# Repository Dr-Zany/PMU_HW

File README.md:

# PMU_HW
Hardware for the PMU

LP2950CZ-5.0/NOPB

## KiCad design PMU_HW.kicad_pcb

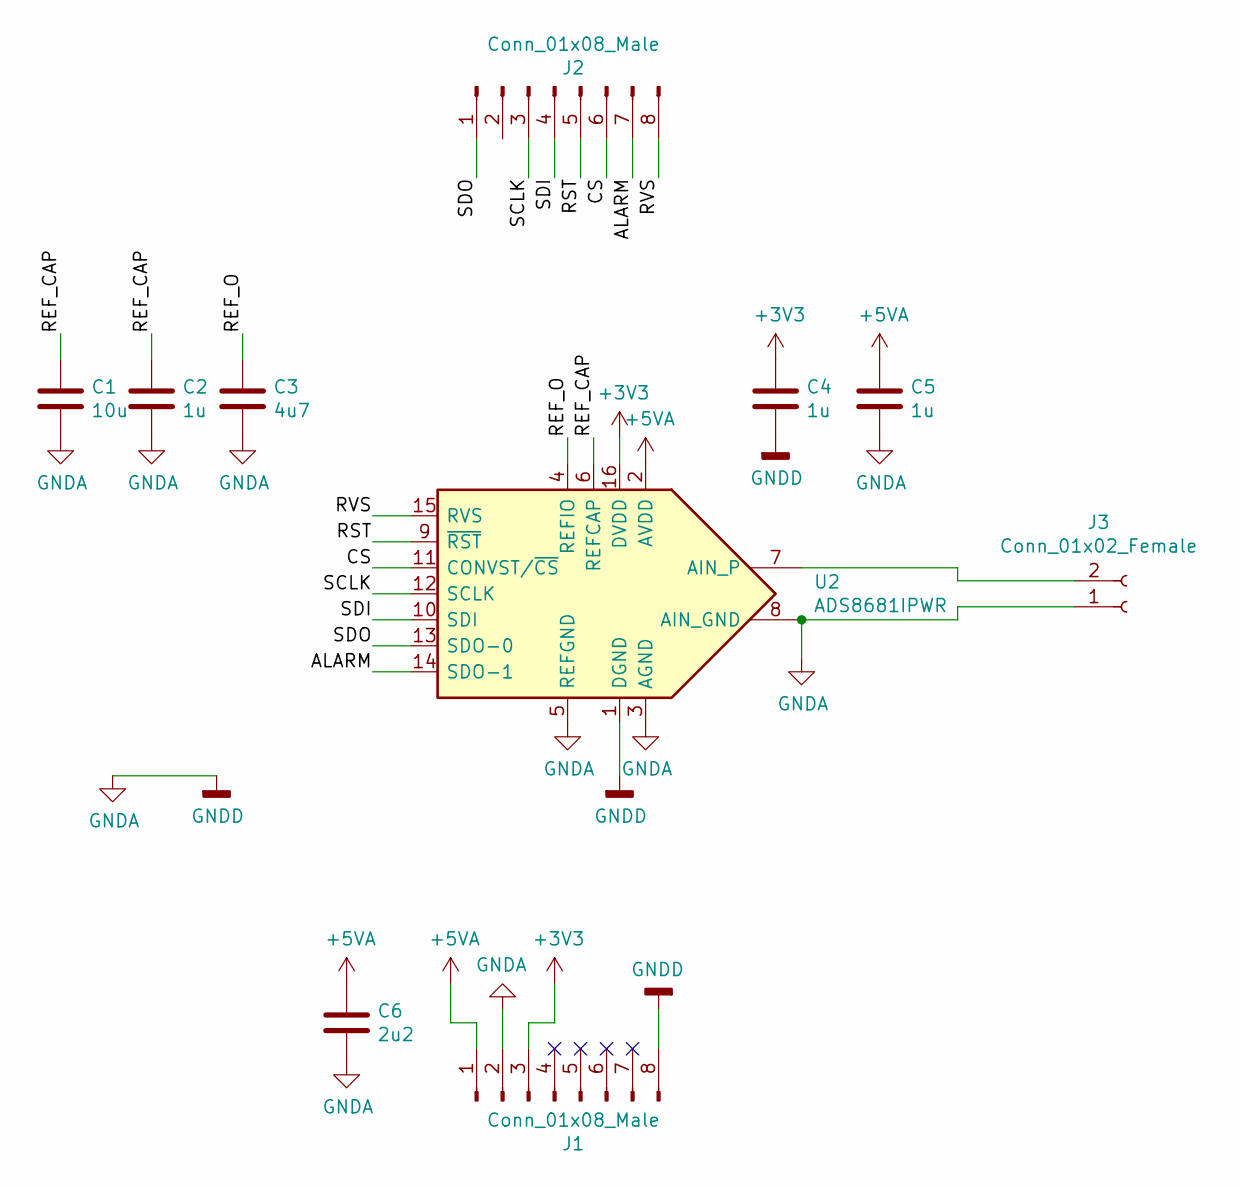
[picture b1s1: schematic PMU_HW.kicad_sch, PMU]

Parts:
C1: 10u; C_0805_2012Metric_Pad1.18x1.45mm_HandSolder
C2, C4, C5: 1u; C_0603_1608Metric_Pad1.08x0.95mm_HandSolder
C3: 4u7; C_0805_2012Metric_Pad1.18x1.45mm_HandSolder
C6: 2u2; C_0603_1608Metric_Pad1.08x0.95mm_HandSolder
J1, J2: Conn_01x08_Male; PinHeader_1x08_P2.54mm_Vertical
J3: Conn_01x02_Female; PinHeader_1x02_P2.54mm_Horizontal
U2: ADS8681IPWR; TSSOP-16_4.4x5mm_P0.65mm

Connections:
+3V3: C4.1, J1.3, U2.16 (DVDD)
+5VA: C5.1, C6.1, J1.1, U2.2 (AVDD)
/ALARM: J2.7, U2.14 (SDO-1)
/CS: J2.6, U2.11 (CONVST/~CS)
/REF_CAP: C1.1, C2.1, U2.6 (REFCAP)
/REF_O: C3.1, U2.4 (REFIO)
/RST: J2.5, U2.9 (~RST)
/RVS: J2.8, U2.15 (RVS)
/SCLK: J2.3, U2.12 (SCLK)
/SDI: J2.4, U2.10 (SDI)
/SDO: J2.1, U2.13 (SDO-0)
GNDA: C1.2, C2.2, C3.2, C4.2, C5.2, C6.2, J1.2, J1.8, J3.1, U2.1 (DGND), U2.3 (AGND), U2.5 (REFGND), U2.8 (AIN_GND)
unnamed: J3.2, U2.7 (AIN_P)

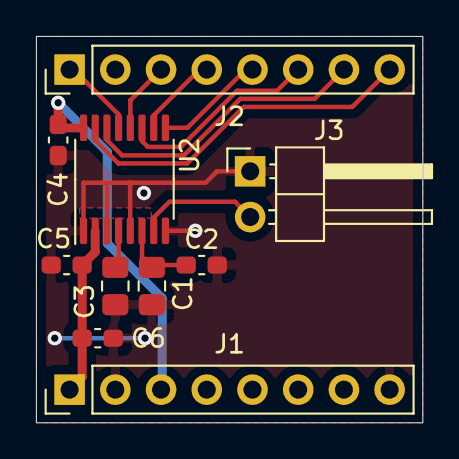
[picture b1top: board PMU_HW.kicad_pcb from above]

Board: 2 copper layers, 21.5 x 21.5 mm, 10 parts (0 on the bottom side), 13 nets.

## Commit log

2021-12-13 added kicad project
2021-12-13 deleted usless folder
2022-01-17 stuff
2022-01-18 fixing git
2022-01-18 finished
2022-01-22 clean up
2022-01-22 more clean up
